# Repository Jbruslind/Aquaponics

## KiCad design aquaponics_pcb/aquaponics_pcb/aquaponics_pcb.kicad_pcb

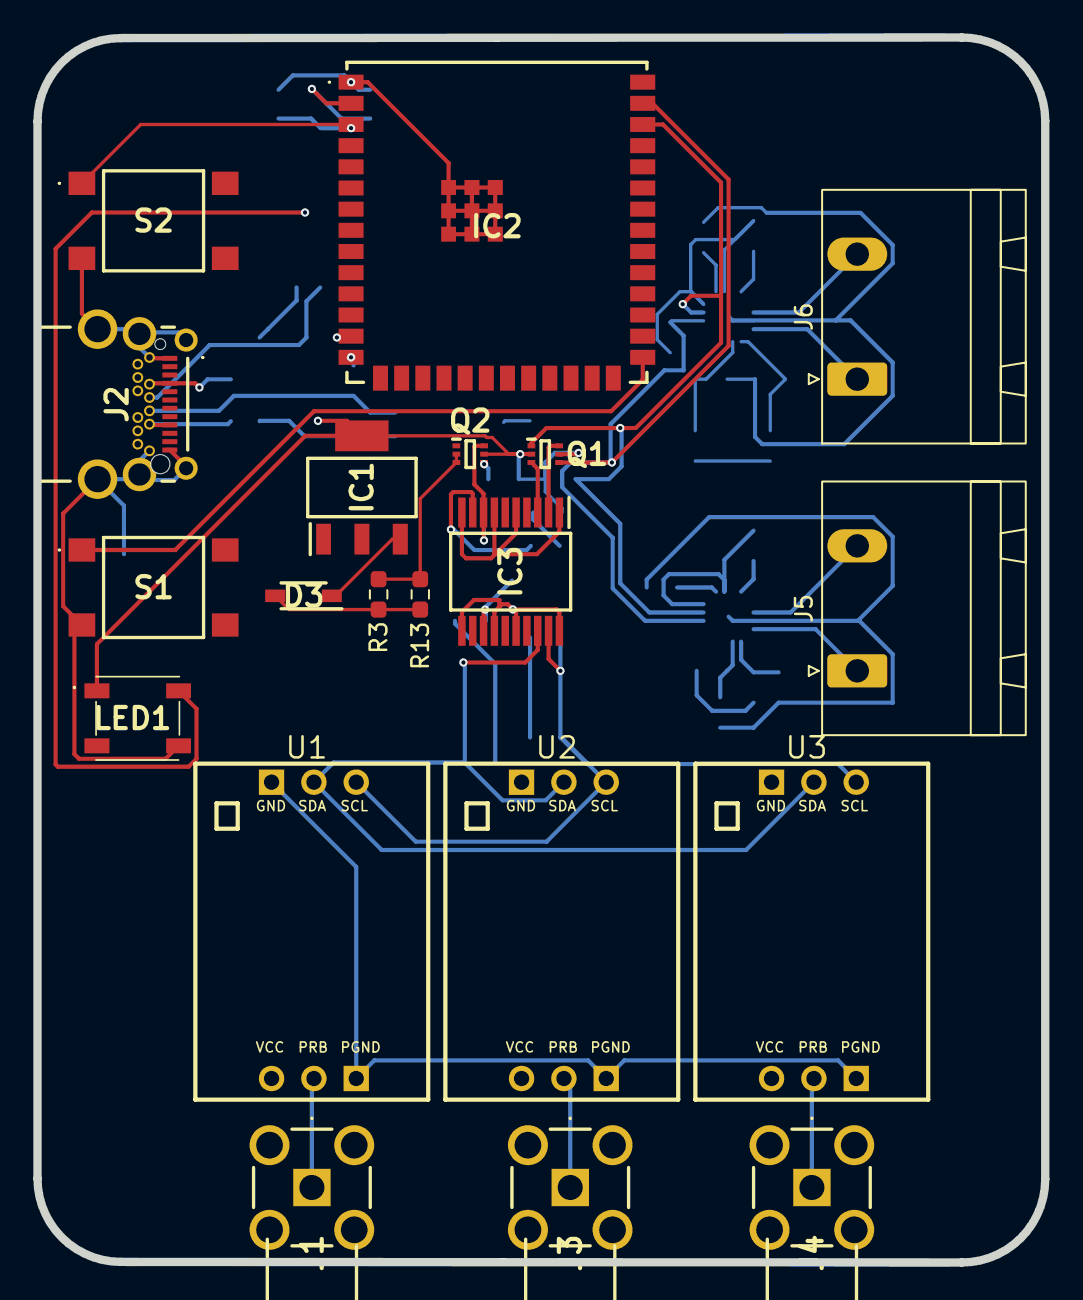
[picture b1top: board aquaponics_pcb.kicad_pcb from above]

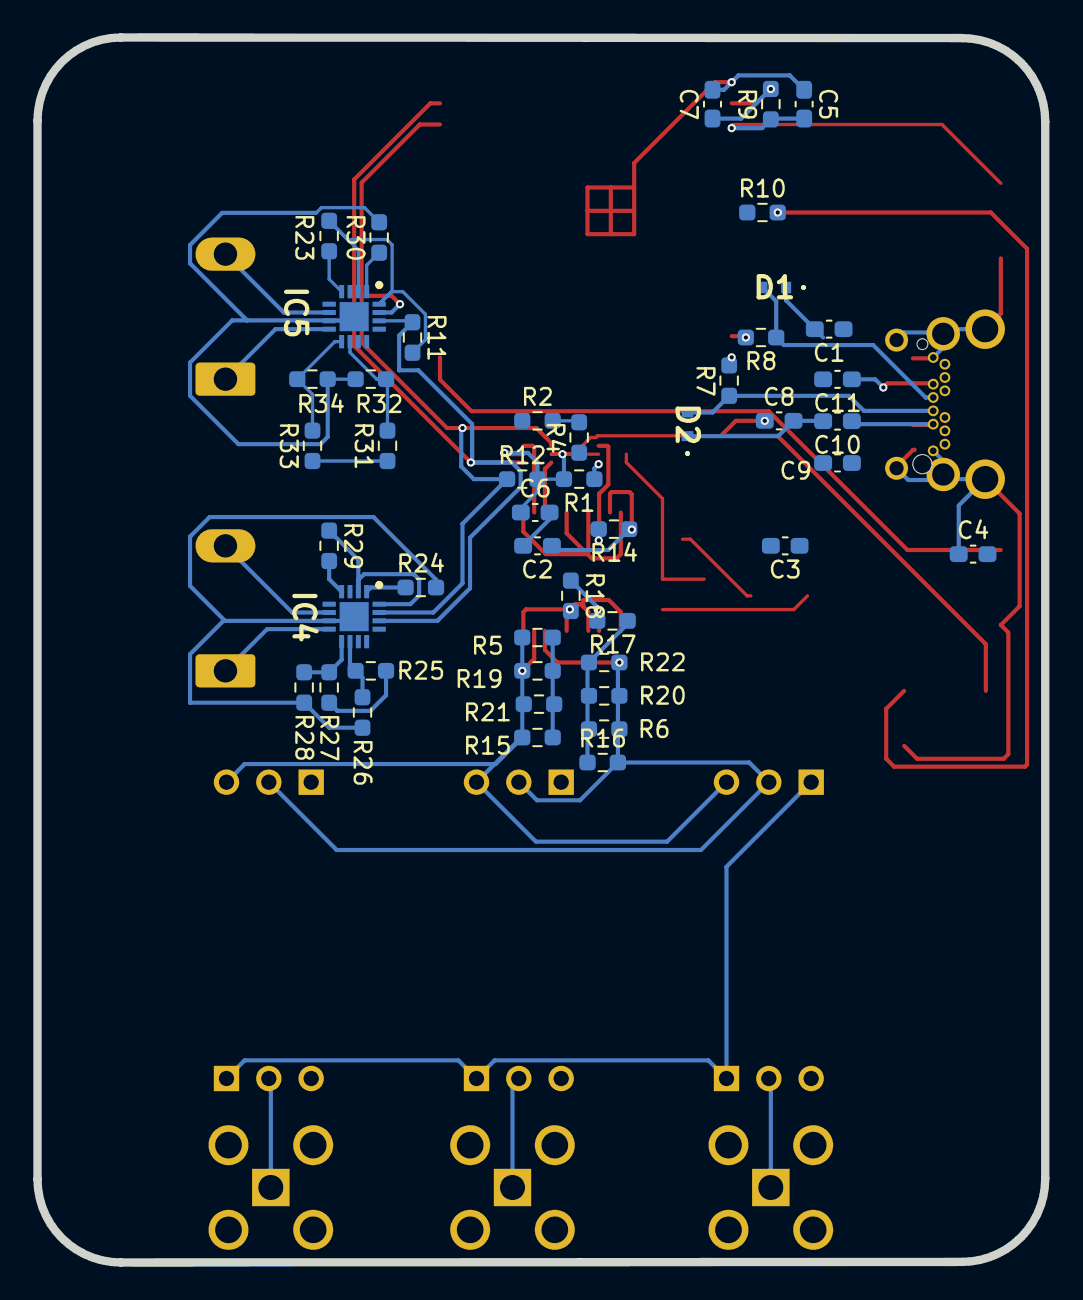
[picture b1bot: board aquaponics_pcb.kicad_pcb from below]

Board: 2 copper layers, 60.5 x 73.5 mm, 67 parts (47 on the bottom side), 43 nets.

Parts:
C1, C6, C9: 10uF; C_0603_1608Metric_Pad1.08x0.95mm_HandSolder
C2, C4, C5, C7, C10: 1uF; C_0603_1608Metric_Pad1.08x0.95mm_HandSolder
C3, C8, C11: 100nF; C_0603_1608Metric_Pad1.08x0.95mm_HandSolder
D1, D2: CPDH5V0P-HF; CPDH5V0PHF
D3: 1N5819HW-7-F; SOD3716X145N
IC1: AZ1117CH-3.3TRG1; SOT230P700X180-4N
IC2: ESP32-S3-WROOM-1U-N8; ESP32S3WROOM1UN8
IC3: ADM3260ARSZ; SOP65P780X200-20N
IC4, IC5: DRV8214RTER; QFN50P300X300X80-17N-D
J1, J3, J4: RFPC-SMA27-F; RFPCSMA27F
J2: 2338792-1; 23387921
J5, J6: Screw_Terminal_01x02; PhoenixContact_GMSTBA_2,5_2-G_1x02_P7.50mm_Horizontal
LED1: WS2812B-B; WS2812BB
Q1, Q2: SSM6N35AFE,LF; SOTFL50P160X60-6N
R1, R2, R3, R4, R9, R11, R12, R17, R23, R25, R26, R27, R28, R29, R31, R32, R33, R34: 10k; R_0603_1608Metric_Pad0.98x0.95mm_HandSolder
R5, R6, R15, R16, R18, R19, R20, R21, R22: 4.7k; R_0603_1608Metric_Pad0.98x0.95mm_HandSolder
R7, R8, R10: 0; R_0603_1608Metric_Pad0.98x0.95mm_HandSolder
R13, R14: 1M; R_0603_1608Metric_Pad0.98x0.95mm_HandSolder
R24, R30: 8.45k; R_0603_1608Metric_Pad0.98x0.95mm_HandSolder
S1, S2: TS04-66-50-BK-260-SMT-TR; TS046650BK260SMTTR
U1, U2, U3: Atlas Scientific EZO; EZO FOOTPRINT

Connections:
+5V_USB: C1.1, C2.1, C3.1, C9.1, C10.1, C11.1, D3.2 (A), IC3.4 (VDDP), IC3.9 (VIN), IC4.5 (VM), IC5.5 (VM), J2.A4 (VBUS_1), J2.A9 (VBUS_2), J2.B4 (VBUS_3), J2.B9 (VBUS_4), R2.2, R3.2, R4.2, R13.1, R14.1
/Cond_Subcircuit/RX_(SCL): IC3.19 (SCL1), R5.2, R15.2, R19.2, R21.2, U1.3 (RX_(SCL)), U2.3 (RX_(SCL)), U3.3 (RX_(SCL))
/Cond_Subcircuit/TX_(SDA): IC3.18 (SDA1), R6.2, R16.2, R20.2, R22.2, U1.2 (TX_(SDA)), U2.2 (TX_(SDA)), U3.2 (TX_(SDA))
/ESP32_MCU/EN: C5.2, IC2.3 (EN), R9.1, S2.1 (NO_1)
/ESP32_MCU/GPIO0: C4.2, IC2.27 (RTC_GPIO0/GPIO0), S1.1 (NO_1)
/ESP32_MCU/I2C_0_MCU_SCL: IC2.38 (RTC_GPIO2/GPIO2/TOUCH2/ADC1_CH1), IC4.15 (SCL), IC5.15 (SCL), Q1.1 (S), R12.1
/ESP32_MCU/I2C_0_MCU_SDA: IC2.39 (RTC_GPIO1/GPIO1/TOUCH1/ADC1_CH0), IC4.14 (SDA), IC5.14 (SDA), Q1.4 (S), R11.1
/ESP32_MCU/ISO_EN: IC2.35 (MTMS/GPIO42), Q2.4 (S), R1.1
/ESP32_MCU/LED_DIN: IC2.7 (RTC_GPIO7/GPIO7/TOUCH7/ADC1_CH6), R10.1
/ESP32_MCU/M2_PWM1: IC2.8 (RTC_GPIO15/GPIO15/U0RTS/ADC2_CH4/XTAL_3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), IC5.13 (EN/IN1)
/ESP32_MCU/M2_PWM2: IC2.9 (RTC_GPIO16/GPIO16/U0CTS/ADC2_CH5/XTAL_3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), IC5.12 (PH/IN2)
/ESP32_MCU/MCU_USB_DN: IC2.13 (RTC_GPIO19/GPIO19/U1RTS/ADC2_CH8/CLK_OU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), J2.A7 (DN1), R8.2
/ESP32_MCU/MCU_USB_DP: IC2.14 (RTC_GPIO20/GPIO20/U1CTS/ADC2_CH9/CLK_OU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), J2.A6 (DP1), R7.2
/ESP32_MCU/M_NFAULT: IC2.23 (RTC_GPIO21/GPIO21), IC4.4 (NFAULT), IC5.4 (NFAULT), R23.2, R29.2
/M1_IPROPI: IC2.6 (RTC_GPIO6/GPIO6/TOUCH6/ADC1_CH5), IC4.1 (IPROPI), R24.1
/M1_PMW1: IC2.4 (RTC_GPIO4/GPIO4/TOUCH4/ADC1_CH3), IC4.13 (EN/IN1)
/M1_PMW2: IC2.5 (RTC_GPIO5/GPIO5/TOUCH5/ADC1_CH4), IC4.12 (PH/IN2)
/M2_IPROPI: IC2.17 (RTC_GPIO9/GPIO9/TOUCH9/ADC1_CH8/FSPIHD/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), IC5.1 (IPROPI), R30.1
/NSLEEP: IC2.12 (RTC_GPIO8/GPIO8/TOUCH8/ADC1_CH7/SUBSPIC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), IC4.11 (NSLEEP), IC5.11 (NSLEEP)
/electrical_isolator/ISO_EN: Q2.2 (G), Q2.3 (D), R3.1, R13.2
/electrical_isolator/SCL: IC3.2 (SCL2), Q1.6 (D), R2.1
/electrical_isolator/SDA: IC3.3 (SDA2), Q1.3 (D), R4.1
/electrical_isolator/VISO: IC3.12 (VISO), IC3.17 (VDDISO), R5.1, R6.1, R15.1, R16.1, R17.1, R19.1, R20.1, R21.1, R22.1, U1.4 (VCC), U2.4 (VCC), U3.4 (VCC)
Earth_Clean: IC3.11 (GNDISO_1), IC3.14 (GNDISO_2), IC3.16 (GNDISO_3), IC3.20 (GNDISO_4), J1.2 (GND), J1.3 (GND), J1.4 (GND), J1.5 (GND), J3.2 (GND), J3.3 (GND), J3.4 (GND), J3.5 (GND), J4.2 (GND), J4.3 (GND), J4.4 (GND), J4.5 (GND), R18.2, U1.1 (GND), U1.6 (PGND), U2.1 (GND), U2.6 (PGND), U3.1 (GND), U3.6 (PGND)
GND: C1.2, C2.2, C3.2, C4.1, C5.1, C6.2, C7.2, C8.2, C9.2, C10.2, C11.2, D1.1, D2.1, IC1.1 (ADJ/GND), IC2.1 (GND_1), IC2.40 (GND_2), IC2.41 (GND_3), IC2.42 (GND_4), IC2.43 (GND_5), IC2.44 (GND_6), IC2.45 (GND_7), IC2.46 (GND_8), IC2.47 (GND_9), IC2.48 (GND_10), IC2.49 (GND_11), IC3.1 (GNDP_1), IC3.5 (GNDP_2), IC3.7 (GNDP_3), IC3.10 (GNDP_4), IC4.7 (GND), IC4.17 (EP), IC5.7 (GND), IC5.17 (EP), J2.A1 (GND_1), J2.A12 (GND_2), J2.B1 (GND_3), J2.B12 (GND_4), J2.G1 (GND_5), J2.G2 (GND_6), J2.G3 (GND_7), J2.G4 (GND_8), J2.G5 (GND_9), J2.G6 (GND_10), LED1.3 (VSS), Q2.1 (S), R24.2, R26.2, R28.2, R30.2, R32.2, R34.2, S1.2 (COM_1), S2.2 (COM_1)
unnamed: D3.1 (K), IC1.3 (INPUT)
unnamed: IC3.8 (PDIS), Q2.6 (D), R14.2
unnamed: IC3.13 (VSEL), R17.2, R18.1
unnamed: IC4.10 (A0), R25.2, R26.1
unnamed: IC4.9 (A1), R27.2, R28.1
unnamed: IC4.6 (OUT1), J5.2
unnamed: IC4.8 (OUT2), J5.1
unnamed: IC5.10 (A0), R31.2, R32.1
unnamed: IC5.9 (A1), R33.2, R34.1
unnamed: IC5.6 (OUT1), J6.2
unnamed: IC5.8 (OUT2), J6.1
unnamed: J1.1 (SIG), U1.5 (PRB)
unnamed: D1.2, J2.B7 (DN2), R8.1
unnamed: D2.2, J2.B6 (DP2), R7.1
unnamed: J3.1 (SIG), U2.5 (PRB)
unnamed: J4.1 (SIG), U3.5 (PRB)
unnamed: LED1.4 (DIN), R10.2
V_MCU: C6.1, C7.1, C8.1, IC1.4 (VOUT), IC2.2 (3V3), IC4.2 (VCC), IC4.16 (VREF), IC5.2 (VCC), IC5.16 (VREF), LED1.1 (VDD), Q1.2 (G), Q1.5 (G), Q2.5 (G), R1.2, R9.2, R11.2, R12.2, R23.1, R25.1, R27.1, R29.1, R31.1, R33.1

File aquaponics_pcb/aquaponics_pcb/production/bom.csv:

Designator,Footprint,Quantity,Value,JLCPCB Part #
"C1, C6, C9",0603,3,10uF,C194427
"C10, C2, C4, C5, C7",0603,5,1uF,C15849
"C11, C3, C8",0603,3,100nF,C14663
"D1, D2",CPDH5V0PHF,2,CPDH5V0P-HF,C2443345
D3,SOD3716X145N,1,1N5819HW-7-F,
IC1,SOT230P700X180-4N,1,AZ1117CH-3.3TRG1,
IC2,ESP32S3WROOM1UN8,1,ESP32-S3-WROOM-1U-N8,
IC3,SOP65P780X200-20N,1,ADM3260ARSZ,
"J1, J3, J4",RFPCSMA27F,3,RFPC-SMA27-F,
J2,23387921,1,2338792-1,
"J5, J6","PhoenixContact_GMSTBA_2,5_2-G_1x02_P7.50mm_Horizontal",2,Screw_Terminal_01x02,
LED1,WS2812BB,1,WS2812B-B,
"Q1, Q2",SOTFL50P160X60-6N,2,"SSM6N35AFE,LF",
"R1, R11, R12, R17, R2, R23, R25, R27, R29, R3, R32, R33, R4, R9",0603,14,10k,C98220
"R10, R7, R8",0603,3,0,C2906974
"R13, R14",0603,2,1M,C22935
"R15, R16, R18",0603,3,4.7k,C99782
"R24, R30",0603,2,8.45k,C2933263
"S1, S2",TS046650BK260SMTTR,2,TS04-66-50-BK-260-SMT-TR,
"U1, U2, U3",EZO FOOTPRINT,3,Atlas Scientific EZO,

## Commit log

2026-01-04 initial commit with kicad project
2026-01-04 update ESP32 MCU sch, add LDO and pinouts
2026-01-04 finish MCU and start logic isolation block
2026-01-05 update isolator circuit
2026-01-10 begin motor control sch
2026-01-12 add ezo datasheets, update motor schematic and add 2 motors
2026-01-12 add initial pcb layout
2026-01-23 Update PCB: add ADM3260, replace C3 with SMA connector
    Replaced C3 capacitor footprint with an RFPC-SMA27-F SMA connector and added the ADM3260ARSZ digital isolator (IC3) to the PCB. Updated R3 to a 10k resistor and made related netlist and footprint cha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
2026-01-26 finish ground and power pours. fix rules and run final DRC. export gerbers
